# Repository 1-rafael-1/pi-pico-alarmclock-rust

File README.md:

# Raspberry Pi Pico Alarmclock written in Rust

A fully-featured alarm clock built on a Raspberry Pi Pico W, written in Rust using the Embassy async framework.

<div align="center">

</div>

*Left: Alarm enabled with lightsaber icon indicator. Center: The completed alarm clock showing the OLED display, NeoPixel ring with hour markers, and three illuminated control buttons (green, blue, yellow). Right: Alarm clock in operation with active NeoPixel LEDs displaying the analog clock.*

---

## Features at a Glance

### Core Functionality
- **WiFi Time Sync** - Automatic time synchronization via worldtimeapi.org (refreshed every 6 hours)
- **Alarm System** - Configurable alarm with sunrise light effect and audio playback
- **Visual Display** - 128×64 OLED display with custom Star Wars-inspired font
- **Analog Clock** - 16-LED NeoPixel ring showing hours (red), minutes (green), and seconds (blue)
- **Battery Powered** - 18650 Li-ion battery with USB charging and voltage monitoring

### User-Configurable Settings
- **Volume Control** (0-30) - Adjustable alarm sound volume, persisted to flash
- **LED Brightness** (0-20) - Adjustable NeoPixel clock brightness with live preview
- **Manual Time Setting** - Set time via buttons when WiFi unavailable or for DST adjustments

### Advanced Features
- **Multi-Mode Interface** - Normal, Menu, Settings, Alarm, System Info, and Standby modes
- **Smart Alarm** - Sunrise light effect followed by audio, with randomized button sequence to dismiss
- **Auto-Timeout Protection** - All menus and settings automatically return to Normal mode after 10 seconds of inactivity (with auto-save)
- **Power Management** - Standby mode with task suspension for minimal power consumption
- **Persistent Storage** - All settings saved to flash memory and survive power cycles

---

## Quick Start

### Build and Flash

This project uses **probe-rs** for debugging and flashing via a debug probe (e.g., Raspberry Pi Debug Probe, Picoprobe).

```bash
# Build and flash with probe-rs (recommended)
DEFMT_LOG=warn cargo run --release
```

See the [Building the Project](#building-the-project) section for more details.

### First Use

1. Power on the device - it will initialize and sync time via WiFi
2. Press **Yellow** to open the menu
3. Press **Green** to access Settings
4. Configure your preferences (volume, brightness, etc.)
5. Press **Blue** in Normal mode to set your alarm time
6. Press **Green** in Normal mode to toggle the alarm on/off

See the [User Manual](#user-manual) below for detailed instructions.

---

## Hardware Components

### Main Components
- Raspberry Pi Pico W (microcontroller with WiFi)
- SSD1306 OLED Display (128×64 pixels, I²C)
- DFPlayer Mini MP3 module (DFR0299)
- WS2812B NeoPixel Ring (16 RGB LEDs)
- 3W 8Ω Speaker
- 18650 Li-ion Battery (3350mAh)
- TC4056A Charger Module
- 5V Step-up Converter

### Interface
- 3× LED Ring Push Buttons (12mm, Green/Blue/Yellow)
- Micro SD card (FAT32, for alarm audio)

Complete bill of materials available in the [Components](#components-bill-of-materials) section below.

---

## Project Structure

The project is written in Rust using the Embassy async framework:

- **`src/state.rs`** - System state management
- **`src/event.rs`** - Event channel and event types
- **`src/task/`** - Async tasks for each peripheral and system function
  - `orchestrate.rs` - Central orchestration and state transitions
  - `display.rs` - OLED display management
  - `light_effects.rs` - NeoPixel LED control
  - `sound.rs` - DFPlayer audio control
  - `rtc_manager.rs` - Real-time clock management
  - `alarm_settings.rs` - Flash persistence for settings
  - `time_updater.rs` - WiFi time synchronization
  - And more...
- **`src/utility/`** - Helper functions (DateTime conversion, etc.)
- **`media/`** - Custom BMP graphics for display
- **`circuit/`** - KiCad schematic and PCB design
- **`enclosure/`** - FreeCAD 1.0 design files

### Documentation

```bash
# Generate and view code documentation
cargo doc --open
```

---

## Building the Project

This project uses `defmt` for logging. Log levels are controlled by the `DEFMT_LOG` environment variable.

### Development Build

For development with full logging (requires debug probe):

```bash
cargo build
cargo run
```

### Release Build

**Warnings only** (prevents RTT buffer overflow when running standalone):

```bash
DEFMT_LOG=warn cargo build --release
DEFMT_LOG=warn cargo run --release
```

**Moderate logging** (info and above):

```bash
DEFMT_LOG=info cargo build --release
```

## User Manual

### Button Layout

- **Green Button** (left)
- **Blue Button** (middle)
- **Yellow Button** (right)

---

### Normal Mode (Clock Display)

This is the default mode showing the current time.

| Button | Action |
|--------|--------|
| **Green** | Toggle alarm ON/OFF |
| **Blue** | Enter alarm time setting |
| **Yellow** | Open menu |

**Display shows:**
- Current time (large Star Wars font digits)
- Date and day of week
- Lightsaber icon (if alarm is active)
- Battery level or USB charging indicator

**NeoPixel ring:**
- Red LED = hour hand
- Green LED = minute hand
- Blue LED = second hand
- Colors mix when hands overlap

---

### Setting the Alarm Time

| Button | Action |
|--------|--------|
| **Green** | Increase hours (+1, wraps 23→0) |
| **Yellow** | Increase minutes (+1, wraps 59→0) |
| **Blue** | Save and return to Normal mode |

**Tips:**
- Hold button for continuous increment
- Time wraps around for easy adjustment
- Alarm setting is saved to flash automatically
- **Auto-timeout:** Returns to Normal mode after 10 seconds of inactivity (changes are saved)

---

### Menu

Press **Yellow** from Normal mode to access the menu.

| Button | Action |
|--------|--------|
| **Green** | **Settings Menu** |
| **Blue** | **Standby Mode** |
| **Yellow** | System Info |

**Auto-timeout:** Returns to Normal mode after 10 seconds of inactivity

---

### Settings Menu

Configure volume, brightness, and time.

| Button | Action |
|--------|--------|
| **Green** | Set Volume |
| **Blue** | Set LED Brightness |
| **Yellow** | Set Time Manually |

**Auto-timeout:** Returns to Normal mode after 10 seconds of inactivity

---

### Set Volume

Adjust alarm sound volume (0-30).

| Button | Action |
|--------|--------|
| **Green** | Increase volume (+1, wraps 30→0) |
| **Yellow** | Decrease volume (-1, wraps 0→30) |
| **Blue** | **Save to flash** and return to Settings Menu |

**Display shows:** `Volume: 13`

**Range:** 0-30 (DFPlayer Mini volume range)

**Auto-timeout:** Auto-saves and returns to Normal mode after 10 seconds of inactivity

---

### Set LED Brightness

Adjust NeoPixel clock brightness (0-20).

| Button | Action |
|--------|--------|
| **Green** | Increase brightness (+1, wraps 20→0) |
| **Yellow** | Decrease brightness (-1, wraps 0→20) |
| **Blue** | **Save to flash** and return to Settings Menu |

**Display shows:** `LED Clock: 1`

**Range:** 0-20 (limited for battery safety)

**Live Preview:** Clock LEDs update immediately as you adjust!

**Auto-timeout:** Auto-saves and returns to Normal mode after 10 seconds of inactivity

---

### Set Time Manually

Set time when WiFi is unavailable or for DST adjustments.

| Button | Action |
|--------|--------|
| **Green** | Increase hours (+1, wraps 23→0) |
| **Yellow** | Increase minutes (+1, wraps 59→0) |
| **Blue** | **Set RTC** and return to Settings Menu |

**Display shows:** Time in large digits (HH:MM)

**Note:** Seconds are reset to :00, date is preserved from current RTC

**Auto-timeout:** Auto-saves and returns to Normal mode after 10 seconds of inactivity

---

### System Info

View power and alarm information (2 pages).

**Page 1 - Power Info:**
- Vsys voltage
- USB power status
- Firmware version

**Page 2 - Alarm Info:**
- Alarm time
- Next trigger date
- Enabled status

| Button | Action |
|--------|--------|
| **Green** | Next page (or exit if on last page) |
| **Blue** | Back to Normal mode |
| **Yellow** | Back to Normal mode |

**Auto-timeout:** Returns to Normal mode after 10 seconds of inactivity

---

### Alarm Triggered

When the alarm goes off:

1. **Sunrise Effect** - NeoPixel ring gradually lights up (morning red → warm white)
2. **Audio Playback** - Imperial March plays once
3. **Waker Effect** - Rainbow whirl on NeoPixel ring
4. **Dismissal Challenge** - Must press randomized button sequence

**Display shows:** `Press Yellow!` (or Green/Blue - changes each time)

| Button | Action |
|--------|--------|
| **Any** | Press the **requested color** in the correct sequence |

**Must press all 3 colors in the correct order to stop the alarm!**

---

### Standby Mode

Power-saving mode with display and LEDs off.

**To enter:** Menu → Blue button

**Display shows:** "Going to sleep..." (briefly)

**What's suspended:**
- Display updates
- NeoPixel ring
- Scheduler task
- Time updater task
- Voltage measurement task

| Button | Action |
|--------|--------|
| **Any** | Wake up device |

**On wake:** All tasks resume and time sync is performed.

---

### Common Patterns

**Navigation:**
- **Yellow** = "Back" or "Next option"
- **Blue** = "Confirm/Save"
- **Green** = "Primary action" or "Increase"

**Adjusting Values:**
- **Green** = Increment/Increase
- **Yellow** = Decrement/Decrease
- **Blue** = Save/Confirm

**Wrapping Behavior:**
All numeric values wrap around for easy adjustment:
- Hours: 23 → 0
- Minutes: 59 → 0
- Volume: 30 → 0
- Brightness: 20 → 0

---

### Tips and Tricks

1. **Settings Persist** - Volume and brightness are saved to flash and survive power cycles
2. **Live Preview** - LED brightness changes are visible immediately while adjusting
3. **No Confirmation Prompts** - Pressing Blue always saves/confirms
4. **Auto-Timeout Protection** - All menus and settings automatically return to Normal mode after 10 seconds of inactivity (settings are auto-saved)
5. **WiFi Not Required** - Manual time setting works even if WiFi is down
6. **Alarm Preserved** - Setting time manually doesn't affect your alarm settings
7. **Hold for Speed** - Hold Green or Yellow buttons for continuous increment

---

## Circuit Design

Circuit schematic available in KiCad format: [circuit/pi-pico-alarmclock/](circuit/pi-pico-alarmclock/)

Design includes:
- Power management with battery charger
- Voltage level sensing
- MOSFET switching for display and audio control
- All peripheral connections

---

## Enclosure

Designed in FreeCAD 1.0. Export files available: [enclosure/](enclosure/)

### Enclosure CAD View

*External view of the enclosure showing the front panel with OLED display cutout, NeoPixel ring hour markers, speaker grille, rotary encoder, and push button positions.*

### Assembly View

*Interior assembly view with lid removed, showing PCB placement, speaker mounting, and 18650 battery holder positioning.*

---

## Assembly

### Breadboard Prototype

*Early breadboard prototype used for development and testing of the circuit design before moving to the final PCB implementation.*

### Finished Build

*The completed alarm clock showing the internal assembly with custom PCB, Raspberry Pi Pico W mounted on the controller board, DFPlayer Mini MP3 module, NeoPixel ring, speaker, 18650 battery, and wiring for the three LED ring push buttons.*

---

## Components (Bill of Materials)

### Main Components
|Component|Qty|Description|
|---------|---|-----------|
|Raspberry Pi Pico W|1|Microcontroller with WiFi|
|OLED Display|1|SSD1306 compatible I²C OLED Display 128×64 pixels with two color yellow/blue. Input Voltage 3.3V|
|DFPlayer Mini|1|MP3 module (DFR0299)|
|TC4056A Charger Module|1|Li-ion battery charging module with protection|
|Step-up Converter|1|5V boost converter (e.g., U3V16F5 or similar), 2.5-5.5V input, 5V/1A output|
|WS2812B NeoPixel Ring|1|16 RGB LED ring (this is the limit the power supply can handle)|
|Speaker|1|3W 8Ω speaker, 70×30×15mm (DFPlayer Mini compatible)|
|18650 Li-ion Battery|1|3350mAh or similar capacity|
|Battery Holder|1|For 18650 battery|
|Micro SD Card|1|Any capacity, formatted to FAT32|

### Push Buttons
|Component|Qty|Description|
|---------|---|-----------|
|LED Ring Push Buttons|3|12mm LED ring illuminated push buttons with JST 4-pin connectors (one each: yellow, green, blue). LED rings are controlled via MOSFET Q4 (IRLZ44N) on GPIO 26 with 10-second auto-off timeout on button press (except during alarm mode)|

### Semiconductors
|Component|Qty|Type|Description|
|---------|---|----|-----------| 
|Q1, Q2, Q4|3|IRLZ44N|N-channel MOSFET, logic-level (TO-220)|
|Q3|1|IRF9540|P-channel MOSFET, logic-level (TO-220)|
|D3|1|1N5819|Schottky diode, 40V, 1A (DO-41)|

### Resistors (1/4W)
|Reference|Qty|Value|
|---------|---|-----|
|R1, R5, R14|3|10kΩ|
|R2, R13|2|100Ω|
|R3, R7|2|1kΩ|
|R6|1|2.2kΩ|
|R8|1|220Ω|
|R9, R11|2|100kΩ|
|R10, R12|2|220kΩ|

### Capacitors
|Reference|Qty|Type|Value|Voltage|Description|
|---------|---|----|-----|-------|-----------|
|C1, C3, C4, C5, C6|5|Ceramic|100nF|50V|General decoupling|
|C2, C7|2|Electrolytic|470µF|16V|Power supply filtering|
|C8, C9|2|Ceramic|100nF|50V|ADC input filters for VSYS/VBUS voltage dividers|

### Connectors
|Reference|Qty|Type|Description|
|---------|---|----|-----------|
|J1|1|Screw Terminal 2P|5mm pitch, for speaker connection|
|J2|1|JST PH 4-pin|Button Green (2mm pitch)|
|J3|1|JST PH 4-pin|Button Blue (2mm pitch)|
|J4|1|JST PH 4-pin|Button Yellow (2mm pitch)|
|J5|1|JST PH 3-pin|NeoPixel connection (2mm pitch)|
|J6|1|JST PH 4-pin|OLED display (2mm pitch)|
|J7|1|Screw Terminal 2P|5mm pitch, for battery connection|

---

## Technical Details

### Power Detection Noise Filtering

The USB power and battery voltage detection uses voltage dividers (220kΩ/100kΩ) with 100nF filter capacitors that help reduce electrical noise from NeoPixel switching and EMI in the enclosure. Software filtering further improves stability:

**USB Detection (VBUS):**
- Debouncing with 5 consecutive readings
- 10ms delay between samples
- Rejects transient noise spikes

**Voltage Measurement (VSYS):**
- Median filter for ADC samples (rejects impulse noise spikes)
- 5ms settling delay between samples
- 0.1V hysteresis to prevent display flicker

### Flash Memory Layout

Settings are stored using sequential-storage with wear leveling:

| Key | Setting | Type | Range | Default |
|-----|---------|------|-------|---------|
| 0 | Alarm Hour | u8 | 0-23 | 0 |
| 1 | Alarm Minute | u8 | 0-59 | 0 |
| 2 | Alarm Enabled | u8 | 0-1 | 0 (false) |
| 3 | Volume | u8 | 0-30 | 13 |
| 4 | Clock Brightness | u8 | 0-20 | 1 |

**Flash Range:** `0x1F_9000..0x1FC_000` (12K allocated)

**Memory Configuration:**
- Total Flash: 2048K (2 MB)
- Code: 2020K
- Settings: 12K
- Reserved: 16K

---

## Lessons Learned for Future Iterations

This project worked well as a learning experience, but there are several hardware design decisions that should be improved in a future version:

### Power Management Issues

**1. No Hardware Power Switch**
- The device lacks a physical power switch, relying entirely on software standby mode
- This means the device continuously draws power even when "off"
- **Solution for next version:** Add a physical power switch between the battery and the circuit OR even better add circuitry to power down and back up by push button, AFAIK that is possible but was out of my league for this iteration.

## Acknowledgments

This is a hobby project and I have very little experience in electronics and had none before in Rust and also none before in CAD. All three things I taught myself along the way. While this was incredible fun, this project will be full of imperfections, literally everywhere. In case you happen across this repo and spots a thing to improve - if you find the time to let me know, I will be more than happy. After all, this was and is about learning things.

That being said: This device does work, at least as far as I did test it to this point.

Does the world need another alarm clock? Hell no, it does not. You can buy them in thousands of types for very little money and then most will have more functionality, better battery life, and whatnot. I was looking for a thing to do, had a joking conversation with my eldest daughter (who is in an age range where getting up in the morning appears to be terribly difficult) and that was that: I found myself building this thing.

It took me two years, much of which time this project sat in some state of being unfinished. Mostly it sat idle when I had hit a wall in Rust-skill, electronics skill or 3d-printing skill. I only very recently found a huge ground bounce that messed up the DFPlayer audio output.

When I started this, Coding AI was in relative infancy. I am glad it was, because that made me learn a lot the hard and memorable way. By today all that I do uses AI to some extent, it is amazing what kind of reach this bestows. So, in this iteration of the project I did use AI for almost all refactoring and - shame on me - also for some features. Would I dare to if this was a commercial project? No. But for a hobby thing? Why not?

## Thanks

- **[Embassy Framework](https://github.com/embassy-rs/embassy)** - Rust async framework for embedded devices with excellent examples and HALs
- **Embassy Community** - Patient and helpful individuals who answered my Rust-rookie and Embassy-rookie questions. From the orchestrator pattern through a number of headscratchers with Cells, Mutexes and Sync Primitives.... I learned it all from them.

## License

MIT License - See [LICENSE](LICENSE) file for details

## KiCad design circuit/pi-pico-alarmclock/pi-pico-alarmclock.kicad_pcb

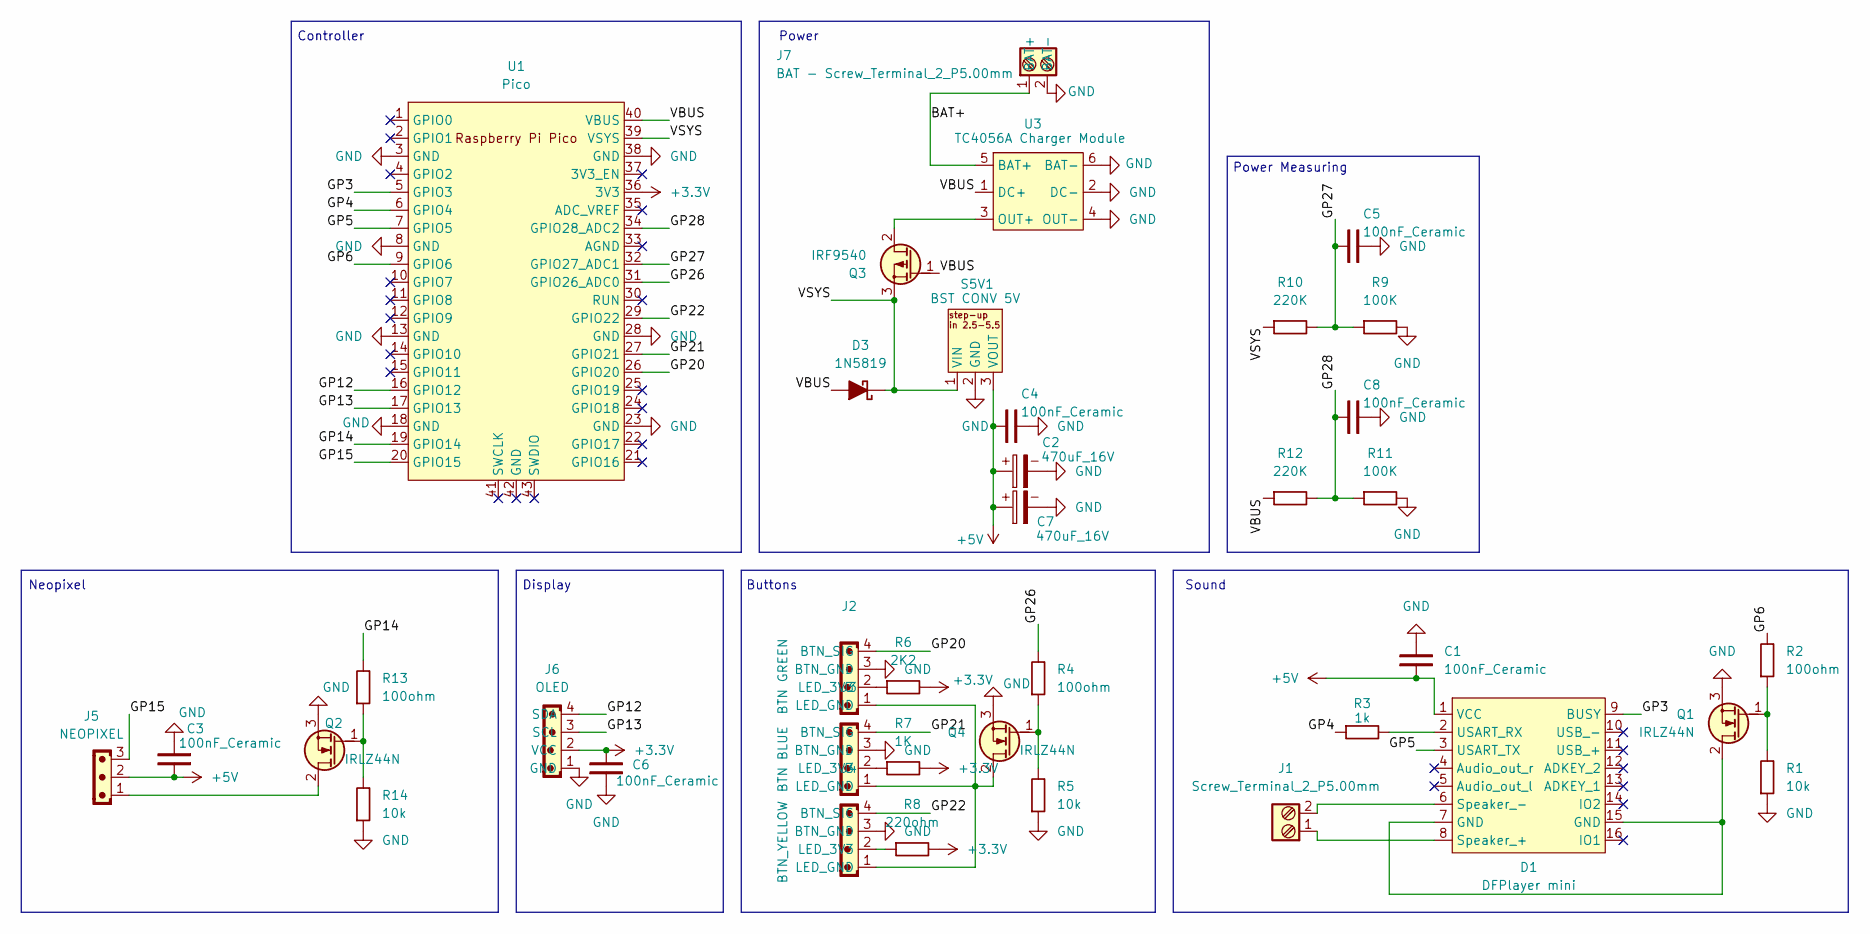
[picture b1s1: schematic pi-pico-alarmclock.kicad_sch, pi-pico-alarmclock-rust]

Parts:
C1, C3, C4, C5, C6, C8: 100nF_Ceramic; C_Disc_D5.0mm_W2.5mm_P2.50mm
C2, C7: 470uF_16V; CP_Radial_D8.0mm_P3.50mm
D1: DFPlayer mini
D3: 1N5819; D_DO-41_SOD81_P7.62mm_Horizontal
J1: Screw_Terminal_2_P5.00mm; TerminalBlock_Phoenix_PT-1,5-2-5.0-H_1x02_P5.00mm_Horizontal
J2: BTN GREEN; JST_PH_B4B-PH-K_1x04_P2.00mm_Vertical
J3: BTN BLUE; JST_PH_B4B-PH-K_1x04_P2.00mm_Vertical
J4: BTN_YELLOW; JST_PH_B4B-PH-K_1x04_P2.00mm_Vertical
J5: NEOPIXEL; JST_PH_B3B-PH-K_1x03_P2.00mm_Vertical
J6: OLED; JST_PH_B4B-PH-K_1x04_P2.00mm_Vertical
J7: BAT - Screw_Terminal_2_P5.00mm; TerminalBlock_Phoenix_PT-1,5-2-5.0-H_1x02_P5.00mm_Horizontal
Q1, Q2, Q4: IRLZ44N; TO-220-3_Vertical_GDS
Q3: IRF9540; TO-220-3_Vertical_GDS
R1, R5, R14: 10k; R_Axial_DIN0207_L6.3mm_D2.5mm_P10.16mm_Horizontal
R2, R4, R13: 100ohm; R_Axial_DIN0207_L6.3mm_D2.5mm_P10.16mm_Horizontal
R3: 1k; R_Axial_DIN0207_L6.3mm_D2.5mm_P10.16mm_Horizontal
R6: 2K2; R_Axial_DIN0207_L6.3mm_D2.5mm_P10.16mm_Horizontal
R7: 1K; R_Axial_DIN0207_L6.3mm_D2.5mm_P10.16mm_Horizontal
R8: 220ohm; R_Axial_DIN0207_L6.3mm_D2.5mm_P10.16mm_Horizontal
R9, R11: 100K; R_Axial_DIN0207_L6.3mm_D2.5mm_P10.16mm_Horizontal
R10, R12: 220K; R_Axial_DIN0207_L6.3mm_D2.5mm_P10.16mm_Horizontal
S5V1: BST CONV 5V; Pololu step-up converter 2.5-5.5V in 5V out
U1: Pico; RaspberryPi_Pico_W_SMD_HandSolder
U3: TC4056A Charger Module; TP4056_charger_board

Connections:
+3.3V: C6.2, J6.2 (VCC), R6.2, R7.2, R8.2, U1.36 (3V3)
+5V: C1.1, C2.1, C3.2, C4.2, C7.1, D1.1 (VCC), J5.2, S5V1.3 (VOUT)
/BAT+: J7.1 (BAT+), U3.5 (BAT+)
/GP3: D1.9 (BUSY), U1.5 (GPIO3)
/GP4: R3.1, U1.6 (GPIO4)
/GP5: D1.3 (USART_TX), U1.7 (GPIO5)
/GP6: R2.2, U1.9 (GPIO6)
/GP12: J6.4 (SDA), U1.16 (GPIO12)
/GP13: J6.3 (SCL), U1.17 (GPIO13)
/GP14: R13.2, U1.19 (GPIO14)
/GP15: J5.3, U1.20 (GPIO15)
/GP20: J2.4 (BTN_SIG), U1.26 (GPIO20)
/GP21: J3.4 (BTN_SIG), U1.27 (GPIO21)
/GP22: J4.4 (BTN_SIG), U1.29 (GPIO22)
/GP26: R4.2, U1.31 (GPIO26_ADC0)
/GP27: C5.2, R9.1, R10.2, U1.32 (GPIO27_ADC1)
/GP28: C8.2, R11.1, R12.2, U1.34 (GPIO28_ADC2)
/VBUS: D3.2 (A), Q3.1 (G), R12.1, U1.40 (VBUS), U3.1 (DC+)
/VSYS: D3.1 (K), Q3.3 (S), R10.1, S5V1.1 (VIN), U1.39 (VSYS)
GND: C1.2, C2.2, C3.1, C4.1, C5.1, C6.1, C7.2, C8.1, J2.3 (BTN_GND), J3.3 (BTN_GND), J4.3 (BTN_GND), J6.1 (GND), J7.2 (BAT-), Q1.3 (S), Q2.3 (S), Q4.3 (S), R1.1, R5.1, R9.2, R11.2, R14.1, S5V1.2 (GND), U1.3 (GND), U1.8 (GND), U1.13 (GND), U1.18 (GND), U1.23 (GND), U1.28 (GND), U1.38 (GND), U3.2 (DC-), U3.4 (OUT-), U3.6 (BAT-)
unnamed: D1.8 (Speaker_+), J1.1
unnamed: D1.6 (Speaker_-), J1.2
unnamed: D1.2 (USART_RX), R3.2
unnamed: J2.2 (LED_3V3), R6.1
unnamed: J2.1 (LED_GND), J3.1 (LED_GND), J4.1 (LED_GND), Q4.2 (D)
unnamed: J3.2 (LED_3V3), R7.1
unnamed: J4.2 (LED_3V3), R8.1
unnamed: D1.7 (GND), D1.15 (GND), Q1.2 (D)
unnamed: Q1.1 (G), R1.2, R2.1
unnamed: J5.1, Q2.2 (D)
unnamed: Q2.1 (G), R13.1, R14.2
unnamed: Q3.2 (D), U3.3 (OUT+)
unnamed: Q4.1 (G), R4.1, R5.2

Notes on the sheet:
Power Measuring
Display
Neopixel
Sound
Buttons
Power
Controller

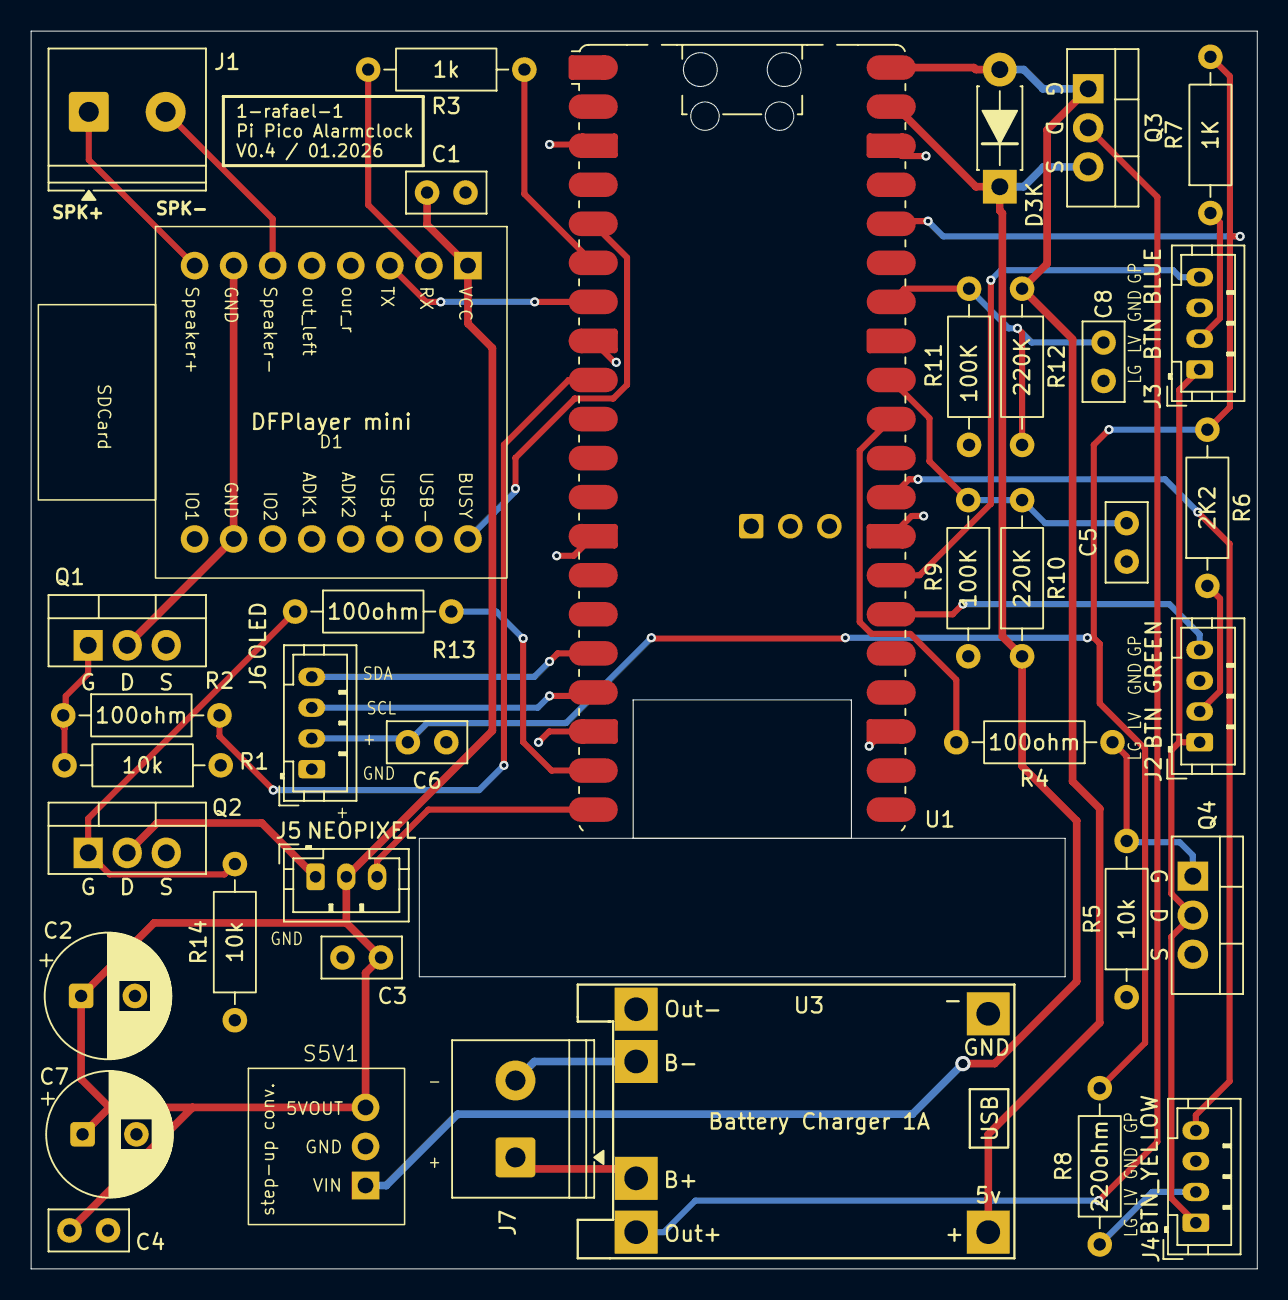
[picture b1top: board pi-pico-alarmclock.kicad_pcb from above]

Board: 2 copper layers, 79.8 x 80.5 mm, 38 parts (0 on the bottom side), 33 nets.

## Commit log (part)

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2024-06-09 use dfmt for tests, add gitignore, add first test file, nocontent
2024-06-09 Create ci.yml (#1)
    * Create ci.yml
    * use dfmt for tests, add gitignore, add first test file, nocontent
    * ci cannot run tests on embedded hardware
    ---------
2024-06-09 can launch and attach debug session
2024-06-13 first implementation of a button task, changes to main including some comments
2024-06-14 upd ci definition
2024-06-14 ci 4
2024-06-14 pdate dependencies and fix cargo build issues
2024-06-15 safely use wifi credentials via build.rs and include! in wifi_mgr
2024-06-15 wifi connects
2024-06-16 Add LICENSE and README files
2024-06-16 StateManager comments
2024-06-16 add time_mgr, still need to refactor wifi_mgr to enable web requests
2024-06-21 cleaning a bit
2024-06-22 we got connection, rettrieve data and have mnaged the strings stuff better
2024-06-23 trying
2024-06-23 typo
2024-06-26 use p instead of peripherals
2024-06-26 clean up
2024-06-27 less lines of main loop message
2024-06-27 10-joining-wifi-stalls-the-system (#11)
2024-07-02 remove all attempts so far
2024-07-02 time_updater some refactoring
2024-07-02 cargo fix
2024-07-02 implemented channel, renamed things; not yet done -> channels so not do what they should yet
2024-07-03 16-put-neopixel-stuff-on-core1 (#24)
2024-07-07 refactoring with peripherlas split, part 1
2024-07-08 refactor 3
2024-07-09 complete media
2024-07-13 better error messages
2024-07-13 we have sound!
2024-07-14 add some module comments
2024-07-15 basic state and orchestrate
2024-07-16 state orchestration works
2024-07-17 update some versions
2024-07-17 Ci-hangs-fix-ci (#30)
2024-07-19 using a mutex for all wifi resources now -> compiles
2024-07-19 more cleanup
2024-07-20 small clean
2024-07-23 warnings
2024-07-23 19-introduce-power-information (#31)
2024-07-24 move config out of src
2024-07-24 33-complete-the-system-states (#35)
2024-07-25 resources
2024-07-26 Remove unused persist_utils module and update module import in state.rs
2024-07-26 implemented task
2024-07-26 cleanup
2024-07-28 set hostname
2024-07-28 extracted orchestrate out of state
2024-07-28 Improve-state-communication (#39)
2024-08-01 Implement-display-layout (#40)
2024-08-03 Add-more-display-things (#41)
2024-08-03 better errors in time_updater
2024-08-03 menu
2024-08-03 standby
2024-08-03 tune vbus edge and vsys voltage
2024-08-04 build opts
2024-08-05 quitting the alarm
2024-08-05 Alarm-and-alarm-stop (#45)
2024-08-07 analog clock works
2024-08-07 improved scheduler: can wake up from downtime. Finished analog clock.
2024-08-08 Trigger vsys voltage reading on usb edge, some tidying (#47)
2024-08-08 sound alarm
2024-08-13 cargo update, needed to set rp2040 feature on embassy-rp
2024-08-14 refactor: Update wifi firmware and power management settings
2024-08-16 ci badge
2024-08-16 finished readme
2024-08-16 fix gallery
2024-08-17 held button sends multiple events down the channel; remove presses which was unused (#54)
2024-08-17 v0.20-alpha; use revisions
2024-08-25 reworked the readme
2024-08-25 slightly rework readme (#58)
2024-08-30 Ws2812-asyn-update (#59)
2025-10-16 Prepare for major refactor -> step 1 update everything
    - Bump Rust edition to 2024 and set toolchain to 1.90.0 - Update embassy
    and related crates to latest git revs - Switch from dfplayer-serial to
    dfplayer-async - Update ws2812-async usage and light effects handler for
    new API - Refactor resource handling to use reborrow and mut where
    needed - Update time_updater for new embassy-net and cyw43 APIs - Add
    RTC interrupt binding and task for static RTC management - Update
2025-10-16 Refactor resource management and remove assign-resources (#63)
    - Remove assign-resources crate and resources module - Inline peripheral
    initialization in main.rs - Update tasks to accept peripherals directly
    - Add rust-analyzer config files for Zed and VSCode - Add clippy lint
    configuration to Cargo.toml - Remove validate_ci.rs test file
2025-10-17 Run all tasks on main executor
    Remove the high-priority InterruptExecutor, SWI_IRQ_1 handler, and the
    core1 spawn. Use the single main spawner for all tasks (including
    light_effects). Update imports accordingly (use defmt::info and drop
    interrupt/multicore types).
2025-10-17 Add package metadata to Cargo.toml
2025-10-18 Make DateTime formatting non-panicking and borrowed
    Change convert_datetime_to_str to take &DateTime and avoid unwraps;
    ignore padding failures so capacity errors skip padding instead of
    panicking. Add a doc comment for StringUtils and update docs to use
    backticks for types. Tweak day-of-week mapping and add a small clippy
    allow for the padding calculation.
2025-10-18 Improve alarm settings flash handling and messages
    Return None when flash read fails; avoid panics and emit warnings
    instead of panicking. Use Option buffer for fetched values, log reads,
    and continue trying to store other values on write failures. Make
    PersistedAlarmSettings::new const and refine its fields. Handle missing
    settings at startup and warn on unexpected commands. Also fix a datetime
    borrow in display, derive Clone for Events, and add a SOUND_STOP_SIGNAL
2025-10-18 Use Ticker for adaptive scheduler timing
    Start with a default Ticker and recreate it when the alarm enabled state
    changes so the scheduler can switch between short and long update
    periods. Wait on ticker.next() or the wake signal instead of a Timer.
2025-10-18 Make StateManager constructors and mutators const
    Also simplify match arms to single-line expressions and remove
    unnecessary braces/semicolons
2025-10-18 Add Eq to Commands and document signals
    Derive Eq for the Commands enum to allow equality checks. Add new
    SCHEDULER_START_SIGNAL and SCHEDULER_WAKE_SIGNAL and improve doc
    comments (use backticks) for vsys_voltage_reader and scheduler signals.
    Remove an obsolete TODO comment.
2025-10-18 Refactor time_updater into modular WiFi/HTTP/RTC
    Extract WiFi and network setup, connection, HTTP fetch, JSON parsing,
    and RTC update into separate functions. Add static cells for CYW43
    state, network stack/resources, and reusable HttpBuffers; use a
    heapless::String for response handling. Improve timeout/error handling,
    retry flow, and overall clarity of the time updater task
2025-10-18 Update config filename in time_updater docs
2025-10-18 Introduce Event channel and per-task signals
2025-10-21 Move state module to src/state and rename types (#68)
2025-10-22 Set rust-analyzer target to thumbv6m-none-eabi
    Disable cargo.allTargets to limit analysis to the specified embedded
    target
2025-11-01 Add button LEDs task and adjust DFPlayer pin
2025-11-02 Update README with flashing instructions and BOM
    Replace elf2uf2-rs steps with picotool flash/uf2 commands and note
    elf2uf2-rs incompatibility with Rust 1.89+. Expand Components into a
    detailed Bill of Materials and point circuit schematic to
    circuit/pi-pico-alarmclock/. Remove binary CDDX and PNG circuit files.
2025-11-02 Document LED ring push buttons in README
2025-11-09 Set drillshape to 0 in KiCad PCB file
2025-11-10 Better schematic (#70)
    * Add button LEDs task and adjust DFPlayer pin
    * Add button LEDs task
    * Add Pi Pico alarm clock KiCad project files
    * Update README with flashing instructions and BOM
    Replace elf2uf2-rs steps with picotool flash/uf2 commands and note
    elf2uf2-rs incompatibility with Rust 1.89+. Expand Components into a
2025-11-10 Use PIO-based WS2812 driver (#71)
    * Use PIO-based WS2812 driver
    * Apply brightness per-LED and optimize iteration
    Compute alarm_brightness once and scale each LED color in the noise
    effect instead of applying brightness to the whole array. Use
    Iterator::take in apply_brightness to avoid a manual bounds check loop.
2025-11-15 worldtimeapi is no longer available
2025-11-16 remove unnessecary kicad files
2025-11-20 Use global signals and mutex for RTC API responses
    Replace per-request oneshot channels with shared Signals and serialize
    callers with RTC_API_MUTEX to avoid responses being stolen. Simplify
    RtcRequest variants to not carry senders and adapt handlers to
    reset/signal responses and use timeouts.
2025-11-20 Test build (#72)
    * move wifi firmware
    * worldtimeapi is no longer available
    * Use PIN_19 for WS2812 light effects
    * remove unnessecary kicad files
    * Add RTC manager and initialization flow
    Replace the global RTC mutex with a dedicated rtc_manager task that owns
2025-11-22 Add system settings, UI and persistence
    Introduce SystemSettings (volume, clock brightness) with flash
    persistence (keys 3-4) and runtime propagation.
    Add UI modes for Settings / SetVolume / SetClockBrightness /
    SetTimeManual, display rendering and button handlers. Provide runtime
    update signals for NeoPixel brightness and DFPlayer volume, and a manual
    RTC-set helper. Refactor settings persistence task to handle both alarm
2025-11-22 Fix typos in README
2025-11-22 Bump version and derive firmware version from Cargo
    Set package version to 0.6.0 and replace hardcoded FIRMWARE_VERSION with
    env!("CARGO_PKG_VERSION")
2025-11-22 remove outdated Fusion360 files
2025-12-05 Eliminate event variants and call handlers directly
    Remove several Event variants (AlarmSettingsNeedUpdate,
    SystemSettingsNeedUpdate, ManualTimeSet, SystemReady, Standby, WakeUp)
    and stop using send_event for settings, RTC and power flows. Convert
    state mutators (toggle_alarm_enabled, set_standby_mode, wake_up) to
    const fns and inline saving/wakeup logic by invoking the appropriate
    handler functions directly.
2025-12-05 Bump dependencies and adapt to Embassy API changes
    Use released embassy and cyw43 crate versions and bump package to 0.7.0.
    Adjust spawn_unwrap to accept a SpawnToken and unwrap internally to
    match the updated embassy-executor API. Specify Grb for PioWs2812 and
    update spawn call sites to unwrap spawn results.
2025-12-11 finished enclosure, pre-testing
2025-12-12 Replace alarm_expirer with DFPlayer busy pin
    Remove alarm_expirer task and its signal/spawn. Make sound_handler
    accept a DFPlayer busy input pin, wait for it to go high to detect
    playback end, and emit Event::AlarmStop. Update main to instantiate and
    pass dfplayer_busy to the sound task.
2025-12-12 Rename busy wait fn to wait_for_music_end
    Import select and Either from embassy_futures::select and use them
    instead of fully-qualified calls
2025-12-12 Bump version to 0.7.1
2025-12-14 some tweaks to the enclosure to make things fit and print better
2025-12-14 Rearrange README images and remove alarm section
2025-12-14 Add noise filtering for power detection
    Use median filtering for VSYS readings, debounce VBUS, and add 0.1V
    hysteresis to suppress display flicker. Add moving_median dependency and
    document the strategy in README
2025-12-14 Add ClockTime and avoid redundant LED writes
2025-12-16 Add Neopixel power control and state handle
    Use PIN_14 to control Neopixel power and pass an explicit NeopixelHandle
    through effects. Ensure proper power-on/off sequencing with small delays
    and update alarm brightness default to 7.
2025-12-16 Move Neopixel control pin from GPIO19 to GPIO15, introduce power management for Neopixel via GPIO14 and another IRLZ44N.
2026-01-06 Update enclosure 3D and CAD files
    Remove stale PiPicoAlarmclock.20251213-100058.FCBak backup
2026-01-06 Update resistors to 220K and bump revision
    Set several 200K resistor values to 220K in schematic and PCB. Bump
    project version/revision to v0.4 (01.2026 / 2026-01-06). Regenerate PCB
    footprint UUIDs.
2026-05-10 Float and restore Neopixel data pin
    Use direct PAC access to switch GP15 to a floating SIO input before
    cutting Neopixel power and restore it to PIO1 before powering on. This
    breaks a parasitic current path through the WS2812B DIN line. PAC access
    is used to avoid re-taking the pin from the PIO (so Flex is not used).
2026-05-12 Dark if alarm active (#83)
    * Float and restore Neopixel data pin
    Use direct PAC access to switch GP15 to a floating SIO input before
    cutting Neopixel power and restore it to PIO1 before powering on. This
    breaks a parasitic current path through the WS2812B DIN line. PAC access
    is used to avoid re-taking the pin from the PIO (so Flex is not used).
    * Bump version to 0.8.0 and update deps
2026-05-14 retries of http requests, timeouts for requests
2026-05-14 new version, reintroduce logs
